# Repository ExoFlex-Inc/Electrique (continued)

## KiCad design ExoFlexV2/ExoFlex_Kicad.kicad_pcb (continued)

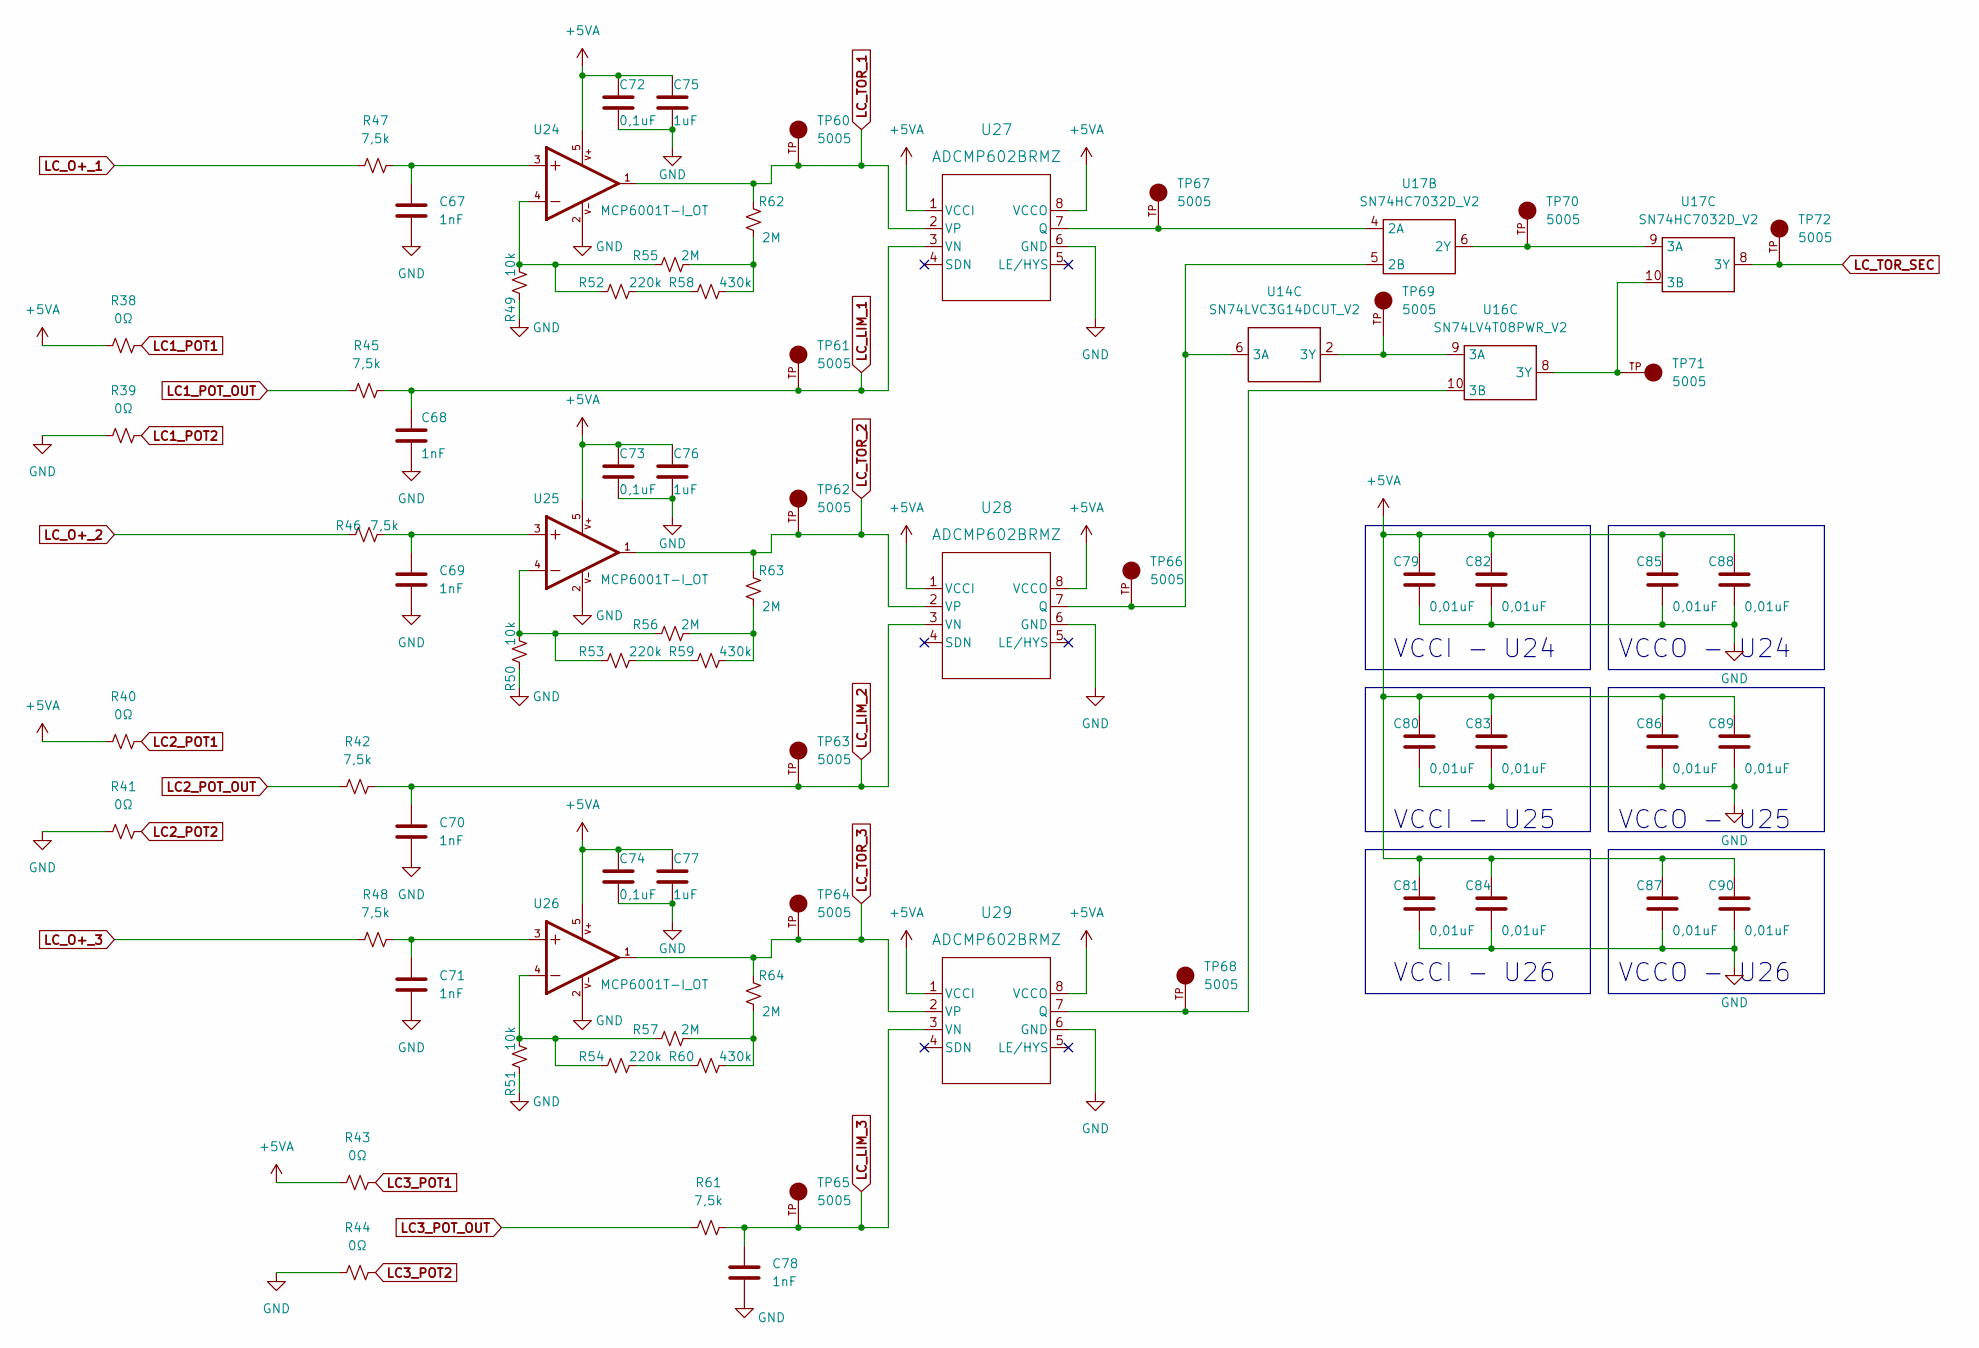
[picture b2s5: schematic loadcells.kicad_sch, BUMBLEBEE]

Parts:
C67, C68, C69, C70, C71, C78: 1nF; C_0603_1608Metric
C72, C73, C74: 0,1uF; C_0603_1608Metric
C75, C76, C77: 1uF; C_0603_1608Metric
C79, C80, C81, C82, C83, C84, C85, C86, C87, C88, C89, C90: 0,01uF; C_0603_1608Metric
R38, R39, R40, R41, R43, R44: 0Ω; R_0603_1608Metric
R42, R45, R46, R47, R48, R61: 7,5k; R_0603_1608Metric
R49, R50, R51: 10k; R_0603_1608Metric
R52, R53, R54: 220k; R_0603_1608Metric
R55, R56, R57, R62, R63, R64: 2M; R_0603_1608Metric
R58, R59, R60: 430k; R_0603_1608Metric
TP60, TP61, TP62, TP63, TP64, TP65, TP66, TP67, TP68, TP69, TP70, TP71, TP72: 5005; KEYSTONE_5005
U14: SN74LVC3G14DCUT_V2; SN74LVC3G14DCUT
U16: SN74LV4T08PWR_V2; SN74LV4T08PWR
U17: SN74HC7032D_V2; SN74HC7032D
U24, U25, U26: MCP6001T-I_OT; SOT95P270X145-5N
U27, U28, U29: ADCMP602BRMZ

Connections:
+5VA: C72.1, C73.1, C74.1, C75.1, C76.1, C77.1, C79.1, C80.1, C81.1, C82.1, C83.1, C84.1, C85.1, C86.1, C87.1, C88.1, C89.1, C90.1, R38.1, R40.1, R43.1, U24.5, U25.5, U26.5, U27.1 (VCCI), U27.8 (VCCO), U28.1 (VCCI), U28.8 (VCCO), U29.1 (VCCI), U29.8 (VCCO); also elsewhere on the board
LC1_POT1: R38.2; also elsewhere on the board
LC1_POT2: R39.2; also elsewhere on the board
LC1_POT_OUT: R45.1; also elsewhere on the board
LC2_POT1: R40.2; also elsewhere on the board
LC2_POT2: R41.2; also elsewhere on the board
LC2_POT_OUT: R42.1; also elsewhere on the board
LC3_POT1: R43.2; also elsewhere on the board
LC3_POT2: R44.2; also elsewhere on the board
LC3_POT_OUT: R61.1; also elsewhere on the board
LC_LIM_1: C68.1, R45.2, TP61.TP, U27.3 (VN); also elsewhere on the board
LC_LIM_2: C70.1, R42.2, TP63.TP, U28.3 (VN); also elsewhere on the board
LC_LIM_3: C78.1, R61.2, TP65.TP, U29.3 (VN); also elsewhere on the board
LC_O+_1: R47.1; also elsewhere on the board
LC_O+_2: R46.1; also elsewhere on the board
LC_O+_3: R48.1; also elsewhere on the board
LC_TOR_1: R62.2, TP60.TP, U24.1, U27.2 (VP); also elsewhere on the board
LC_TOR_2: R63.2, TP62.TP, U25.1, U28.2 (VP); also elsewhere on the board
LC_TOR_3: R64.2, TP64.TP, U26.1, U29.2 (VP); also elsewhere on the board
LC_TOR_SEC: TP72.TP, U17.8 (3Y); also elsewhere on the board
unnamed: C67.1, R47.2, U24.3
unnamed: C69.1, R46.2, U25.3
unnamed: C71.1, R48.2, U26.3
unnamed: R49.2, R52.1, R55.1, U24.4
unnamed: R50.2, R53.1, R56.1, U25.4
unnamed: R51.2, R54.1, R57.1, U26.4
unnamed: R52.2, R58.1
unnamed: R53.2, R59.1
unnamed: R54.2, R60.1
unnamed: R55.2, R58.2, R62.1
unnamed: R56.2, R59.2, R63.1
unnamed: R57.2, R60.2, R64.1
unnamed: TP66.TP, U14.6 (3A), U17.5 (2B), U28.7 (Q)
unnamed: TP67.TP, U17.4 (2A), U27.7 (Q)
unnamed: TP68.TP, U16.10 (3B), U29.7 (Q)
unnamed: TP69.TP, U14.2 (3Y), U16.9 (3A)
unnamed: TP70.TP, U17.6 (2Y), U17.9 (3A)
unnamed: TP71.TP, U16.8 (3Y), U17.10 (3B)

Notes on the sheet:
VCCO - U26
VCCI - U26
VCCO - U25
VCCI - U25
VCCI - U24
VCCO - U24

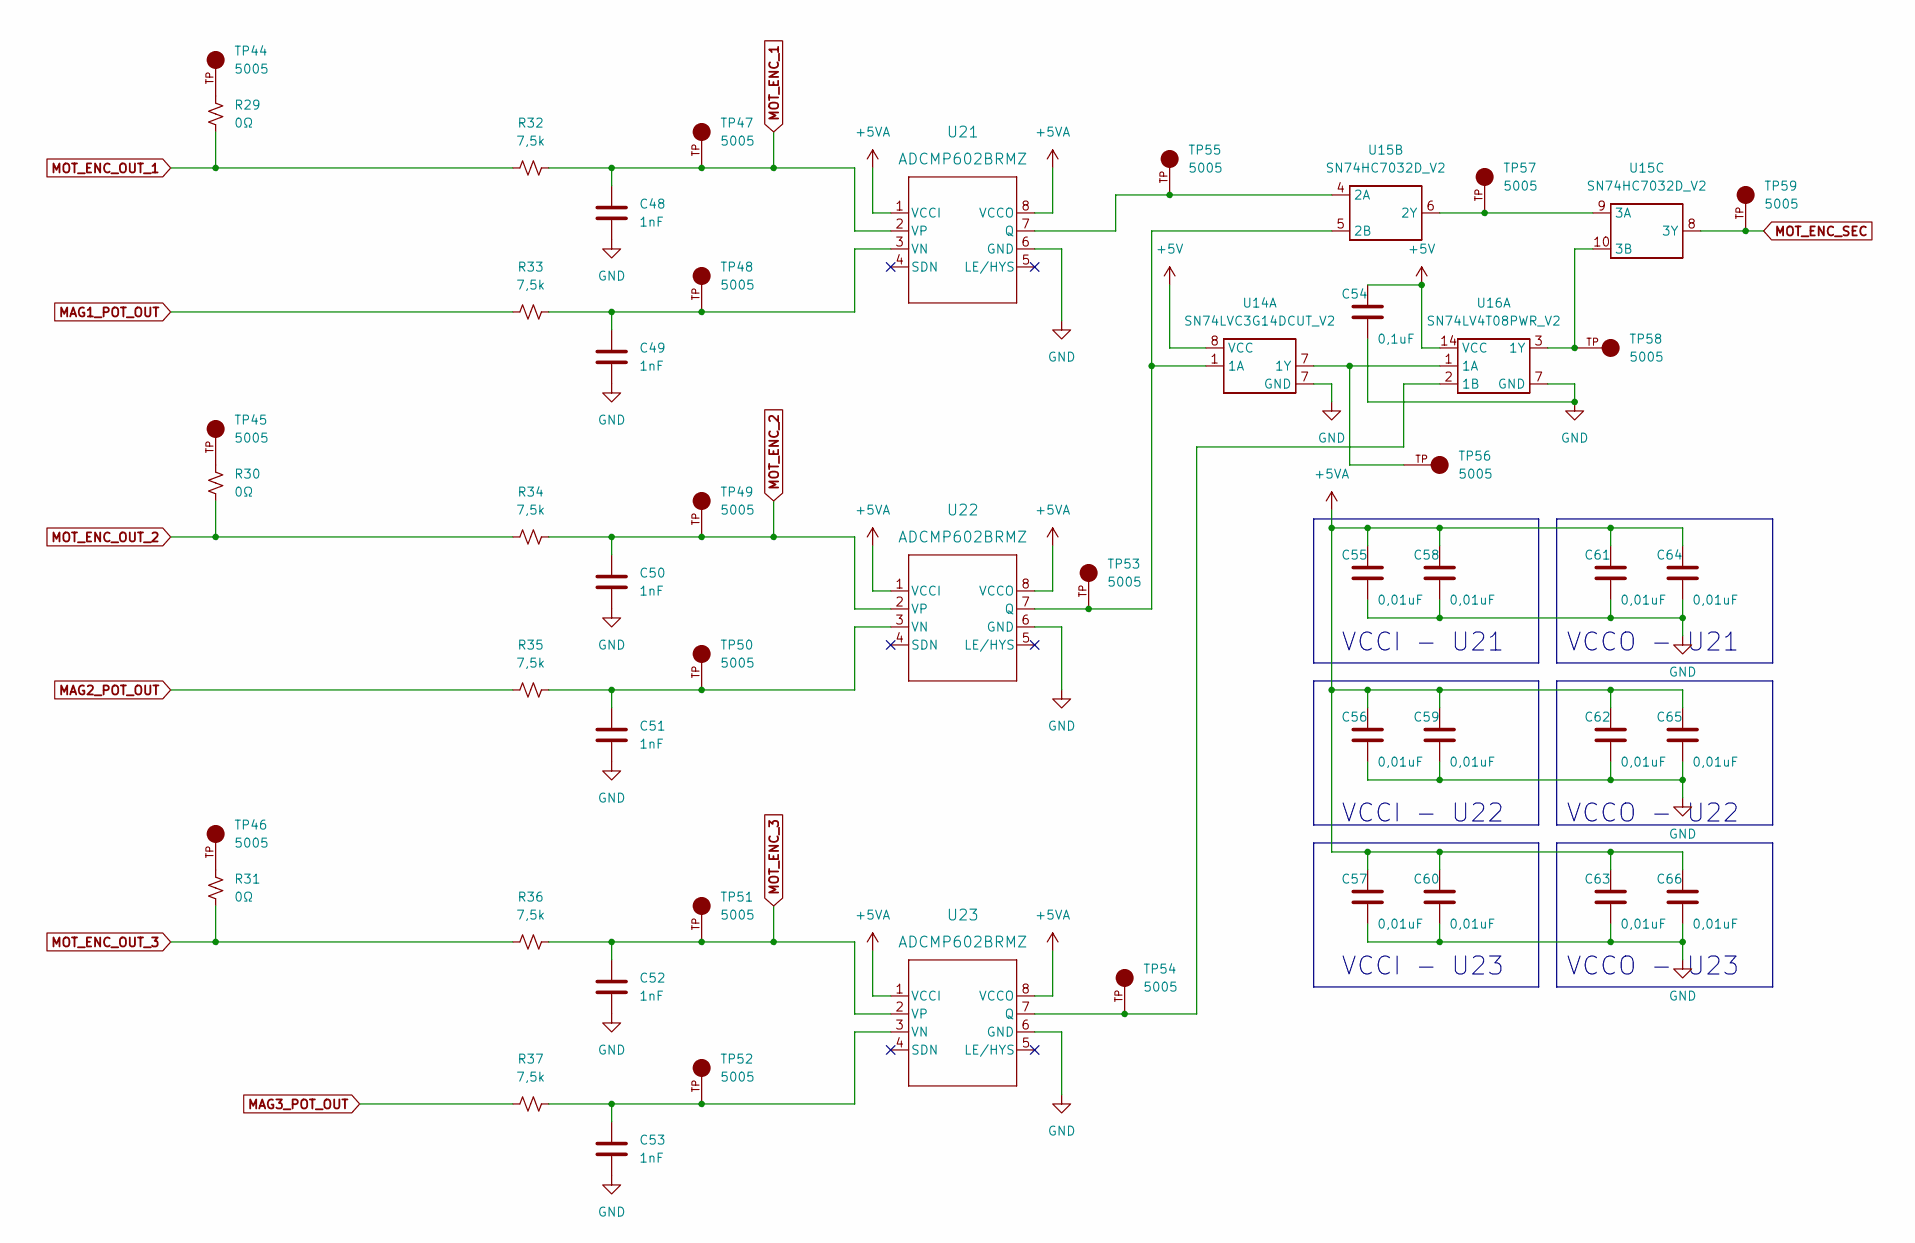
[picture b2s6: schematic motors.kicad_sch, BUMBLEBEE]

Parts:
C48, C49, C50, C51, C52, C53: 1nF; C_0603_1608Metric
C54: 0,1uF; C_0603_1608Metric
C55, C56, C57, C58, C59, C60, C61, C62, C63, C64, C65, C66: 0,01uF; C_0603_1608Metric
R29, R30, R31: 0Ω; R_0603_1608Metric
R32, R33, R34, R35, R36, R37: 7,5k; R_0603_1608Metric
TP44, TP45, TP46, TP47, TP48, TP49, TP50, TP51, TP52, TP53, TP54, TP55, TP56, TP57, TP58, TP59: 5005; KEYSTONE_5005
U14: SN74LVC3G14DCUT_V2; SN74LVC3G14DCUT
U15: SN74HC7032D_V2; SN74HC7032D
U16: SN74LV4T08PWR_V2; SN74LV4T08PWR
U21, U22, U23: ADCMP602BRMZ

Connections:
+5VA: C55.1, C56.1, C57.1, C58.1, C59.1, C60.1, C61.1, C62.1, C63.1, C64.1, C65.1, C66.1, U21.1 (VCCI), U21.8 (VCCO), U22.1 (VCCI), U22.8 (VCCO), U23.1 (VCCI), U23.8 (VCCO); also elsewhere on the board
MAG1_POT_OUT: R33.1; also elsewhere on the board
MAG2_POT_OUT: R35.1; also elsewhere on the board
MAG3_POT_OUT: R37.1; also elsewhere on the board
MOT_ENC_1: C48.1, R32.2, TP47.TP, U21.2 (VP)
MOT_ENC_2: C50.1, R34.2, TP49.TP, U22.2 (VP)
MOT_ENC_3: C52.1, R36.2, TP51.TP, U23.2 (VP)
MOT_ENC_OUT_1: R29.2, R32.1; also elsewhere on the board
MOT_ENC_OUT_2: R30.2, R34.1; also elsewhere on the board
MOT_ENC_OUT_3: R31.2, R36.1; also elsewhere on the board
MOT_ENC_SEC: TP59.TP, U15.8 (3Y); also elsewhere on the board
unnamed: C49.1, R33.2, TP48.TP, U21.3 (VN)
unnamed: C51.1, R35.2, TP50.TP, U22.3 (VN)
unnamed: C53.1, R37.2, TP52.TP, U23.3 (VN)
unnamed: R29.1, TP44.TP
unnamed: R30.1, TP45.TP
unnamed: R31.1, TP46.TP
unnamed: TP53.TP, U14.1 (1A), U15.5 (2B), U22.7 (Q)
unnamed: TP54.TP, U16.2 (1B), U23.7 (Q)
unnamed: TP55.TP, U15.4 (2A), U21.7 (Q)
unnamed: TP57.TP, U15.6 (2Y), U15.9 (3A)
unnamed: TP58.TP, U15.10 (3B), U16.3 (1Y)

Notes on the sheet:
VCCI - U21
VCCO - U21
VCCI - U22
VCCO - U22
VCCI - U23
VCCO - U23

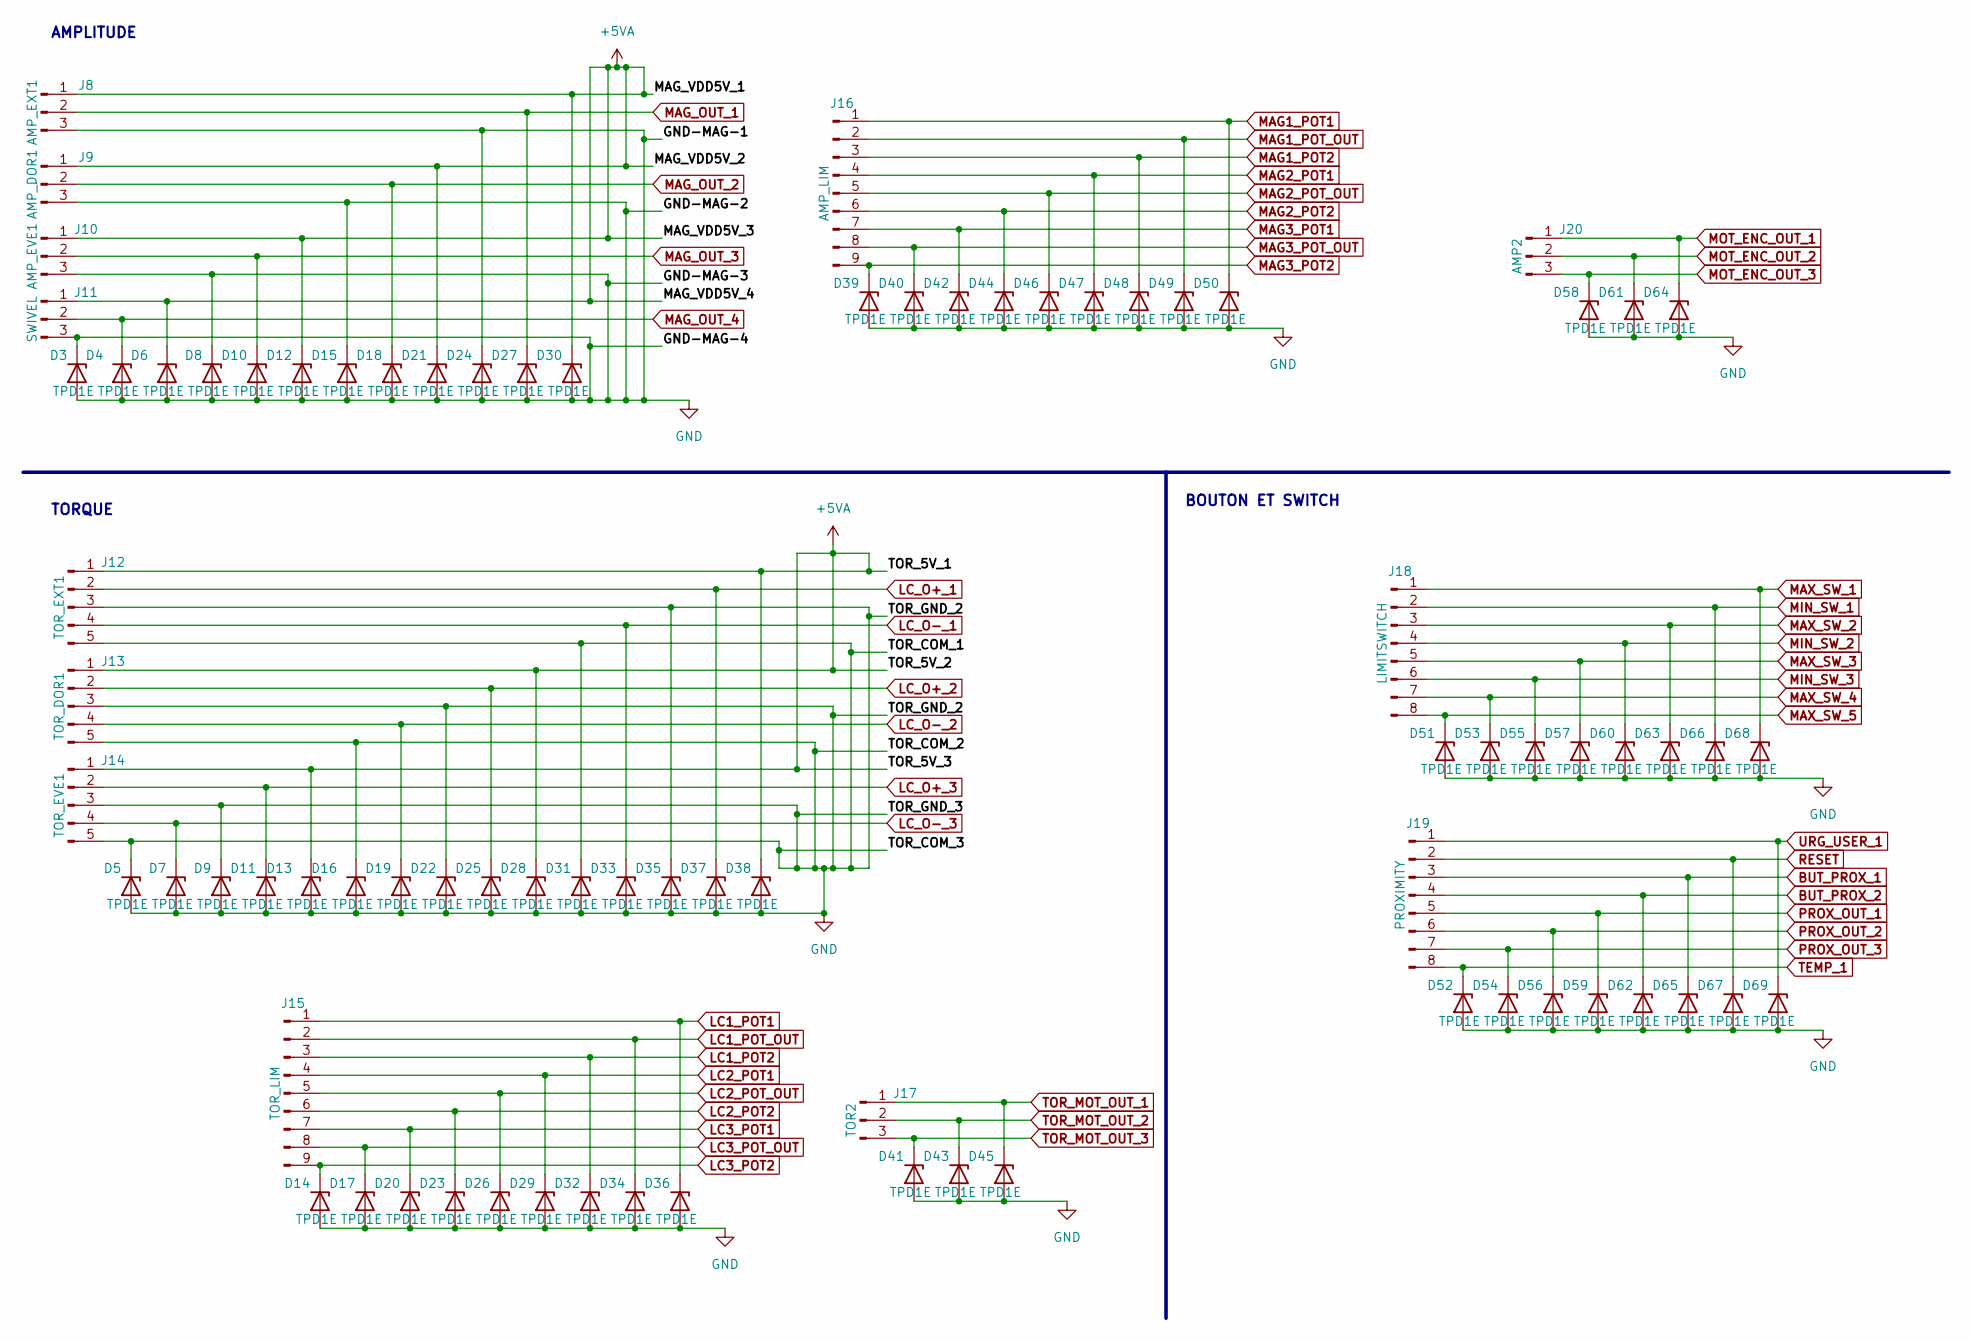
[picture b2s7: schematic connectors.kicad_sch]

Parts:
D3, D4, D5, D6, D7, D8, D9, D10, D11, D12, D13, D14, D15, D16, D17, D18, D19, D20, D21, D22, D23, D24, D25, D26, D27, D28, D29, D30, D31, D32, D33, D34, D35, D36, D37, D38, D39, D40, D41, D42, D43, D44, D45, D46, D47, D48, D49, D50, D51, D52, D53, D54, D55, D56, D57, D58, D59, D60, D61, D62, D63, D64, D65, D66, D67, D68, D69: TPD1E; DPY2_TEX
J8: AMP_EXT1; PinHeader_1x03_P2.54mm_Vertical
J9: AMP_DOR1; PinHeader_1x03_P2.54mm_Vertical
J10: AMP_EVE1; PinHeader_1x03_P2.54mm_Vertical
J11: SWIVEL; PinHeader_1x03_P2.54mm_Vertical
J12: TOR_EXT1; PinHeader_1x05_P2.54mm_Vertical
J13: TOR_DOR1; PinHeader_1x05_P2.54mm_Vertical
J14: TOR_EVE1; PinHeader_1x05_P2.54mm_Vertical
J15: TOR_LIM; PinHeader_1x09_P2.54mm_Vertical
J16: AMP_LIM; PinHeader_1x09_P2.54mm_Vertical
J17: TOR2; PinHeader_1x03_P2.54mm_Vertical
J18: LIMITSWITCH; PinHeader_1x08_P2.54mm_Vertical
J19: PROXIMITY; PinHeader_1x08_P2.54mm_Vertical
J20: AMP2; PinHeader_1x03_P2.54mm_Vertical

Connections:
+5VA: D6.1 (K), D12.1 (K), D13.1 (K), D21.1 (K), D28.1 (K), D30.1 (K), D38.1 (K), J8.1, J9.1, J10.1, J11.1, J12.1, J13.1, J14.1; also elsewhere on the board
BUT_PROX_1: D65.1 (K), J19.3; also elsewhere on the board
BUT_PROX_2: D62.1 (K), J19.4; also elsewhere on the board
LC1_POT1: D36.1 (K), J15.1; also elsewhere on the board
LC1_POT2: D32.1 (K), J15.3; also elsewhere on the board
LC1_POT_OUT: D34.1 (K), J15.2; also elsewhere on the board
LC2_POT1: D29.1 (K), J15.4; also elsewhere on the board
LC2_POT2: D23.1 (K), J15.6; also elsewhere on the board
LC2_POT_OUT: D26.1 (K), J15.5; also elsewhere on the board
LC3_POT1: D20.1 (K), J15.7; also elsewhere on the board
LC3_POT2: D14.1 (K), J15.9; also elsewhere on the board
LC3_POT_OUT: D17.1 (K), J15.8; also elsewhere on the board
LC_O+_1: D37.1 (K), J12.2; also elsewhere on the board
LC_O+_2: D25.1 (K), J13.2; also elsewhere on the board
LC_O+_3: D11.1 (K), J14.2; also elsewhere on the board
LC_O-_1: D33.1 (K), J12.4
LC_O-_2: D19.1 (K), J13.4
LC_O-_3: D7.1 (K), J14.4
MAG1_POT1: D50.1 (K), J16.1; also elsewhere on the board
MAG1_POT2: D48.1 (K), J16.3; also elsewhere on the board
MAG1_POT_OUT: D49.1 (K), J16.2; also elsewhere on the board
MAG2_POT1: D47.1 (K), J16.4; also elsewhere on the board
MAG2_POT2: D44.1 (K), J16.6; also elsewhere on the board
MAG2_POT_OUT: D46.1 (K), J16.5; also elsewhere on the board
MAG3_POT1: D42.1 (K), J16.7; also elsewhere on the board
MAG3_POT2: D39.1 (K), J16.9; also elsewhere on the board
MAG3_POT_OUT: D40.1 (K), J16.8; also elsewhere on the board
MAG_OUT_1: D27.1 (K), J8.2; also elsewhere on the board
MAG_OUT_2: D18.1 (K), J9.2; also elsewhere on the board
MAG_OUT_3: D10.1 (K), J10.2; also elsewhere on the board
MAG_OUT_4: D4.1 (K), J11.2; also elsewhere on the board
MAX_SW_1: D68.1 (K), J18.1; also elsewhere on the board
MAX_SW_2: D63.1 (K), J18.3; also elsewhere on the board
MAX_SW_3: D57.1 (K), J18.5; also elsewhere on the board
MAX_SW_4: D53.1 (K), J18.7; also elsewhere on the board
MAX_SW_5: D51.1 (K), J18.8; also elsewhere on the board
MIN_SW_1: D66.1 (K), J18.2; also elsewhere on the board
MIN_SW_2: D60.1 (K), J18.4; also elsewhere on the board
MIN_SW_3: D55.1 (K), J18.6; also elsewhere on the board
MOT_ENC_OUT_1: D64.1 (K), J20.1; also elsewhere on the board
MOT_ENC_OUT_2: D61.1 (K), J20.2; also elsewhere on the board
MOT_ENC_OUT_3: D58.1 (K), J20.3; also elsewhere on the board
PROX_OUT_1: D59.1 (K), J19.5; also elsewhere on the board
PROX_OUT_2: D56.1 (K), J19.6; also elsewhere on the board
PROX_OUT_3: D54.1 (K), J19.7; also elsewhere on the board
RESET: D67.1 (K), J19.2; also elsewhere on the board
TEMP_1: D52.1 (K), J19.8; also elsewhere on the board
TOR_MOT_OUT_1: D45.1 (K), J17.1; also elsewhere on the board
TOR_MOT_OUT_2: D43.1 (K), J17.2; also elsewhere on the board
TOR_MOT_OUT_3: D41.1 (K), J17.3; also elsewhere on the board
URG_USER_1: D69.1 (K), J19.1; also elsewhere on the board

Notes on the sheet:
BOUTON ET SWITCH
TORQUE
AMPLITUDE

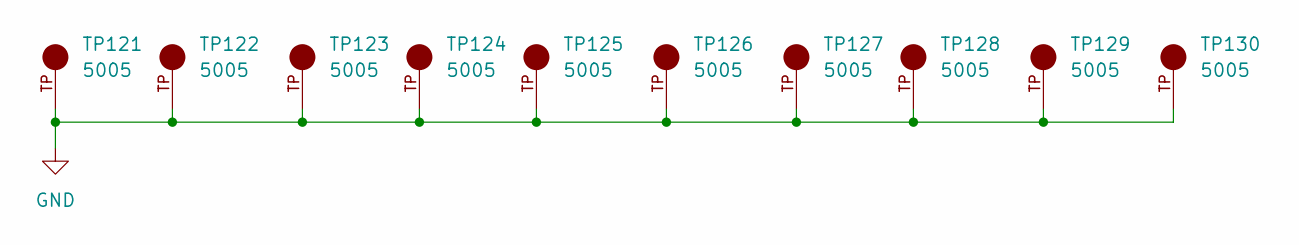
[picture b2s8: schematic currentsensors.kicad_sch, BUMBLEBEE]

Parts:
TP121, TP122, TP123, TP124, TP125, TP126, TP127, TP128, TP129, TP130: 5005; KEYSTONE_5005

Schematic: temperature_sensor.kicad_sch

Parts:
C128, C129: 1nF; C_0603_1608Metric
C130, C131, C132, C133: 0,01uF; C_0603_1608Metric
R91, R93, R94: 0Ω; R_0603_1608Metric
R92, R95: 7,5k; R_0603_1608Metric
TP118, TP119, TP120: 5005; KEYSTONE_5005
U38: ADCMP602BRMZ

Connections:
+5VA: C130.1, C131.1, C132.1, C133.1, R93.1, U38.1 (VCCI), U38.8 (VCCO); also elsewhere on the board
unnamed: C129.1, R95.2, U38.3 (VN)
unnamed: R91.1, TP118.TP
unnamed: R93.2, R94.2, R95.1
TEMP_1: C128.1, R92.2, TP119.TP, U38.2 (VP); also elsewhere on the board
TEMP_OUT_1: R91.2, R92.1
TEMP_SEC: TP120.TP, U38.7 (Q); also elsewhere on the board

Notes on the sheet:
VCCO - U41
VCCI - U41

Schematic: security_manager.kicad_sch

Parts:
C18, C19, C20: 1uF; C_0603_1608Metric
TP10, TP11, TP12, TP13, TP14, TP15, TP16, TP17, TP18, TP19: 5005; KEYSTONE_5005
U7, U8: SN74HC7032D_V2; SN74HC7032D
U9, U10: SN74LV4T08PWR_V2; SN74LV4T08PWR

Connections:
ALIM_SEC: U7.3 (1Y); also elsewhere on the board
BUT_PROX_SEC: U8.13 (4B); also elsewhere on the board
LC_TOR_SEC: U8.1 (1A); also elsewhere on the board
LEFTRIGHT_SEC: U10.2 (1B); also elsewhere on the board
MAG_AMP_SEC: U7.5 (2B); also elsewhere on the board
MOT_ENC_SEC: U7.4 (2A); also elsewhere on the board
unnamed: TP10.TP, U7.6 (2Y), U7.9 (3A)
unnamed: TP11.TP, U7.2 (1B), U7.11 (4Y)
unnamed: TP12.TP, U7.8 (3Y), U9.9 (3A)
unnamed: TP13.TP, U8.3 (1Y), U9.13 (4B)
unnamed: TP14.TP, U8.11 (4Y), U9.10 (3B), U9.12 (4A), U10.1 (1A)
unnamed: TP15.TP, U8.4 (2A), U9.8 (3Y)
unnamed: TP16.TP, U8.5 (2B), U9.11 (4Y)
unnamed: TP17.TP, U8.6 (2Y), U8.9 (3A)
unnamed: TP18.TP, U8.10 (3B), U10.3 (1Y)
unnamed: TP19.TP, U7.1 (1A), U8.8 (3Y)
PROX_SEC: U8.12 (4A); also elsewhere on the board
SW-SEC: U7.10 (3B); also elsewhere on the board
TEMP_SEC: U7.13 (4B); also elsewhere on the board
TOR_MOT_SEC: U8.2 (1B); also elsewhere on the board
URG_SEC: U7.12 (4A); also elsewhere on the board

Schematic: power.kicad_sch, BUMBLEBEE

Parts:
C1, C10, C13, C14, C15, C16, C17: 10uF; C_0603_1608Metric
C2: 150uF 50V; CAP_EEHZS1H151P
C3: 10 uF; C_0805_2012Metric
C4, C7: 0,047uF; C_0603_1608Metric
C5: 100uF 20V; CAP_PC_8X7_NCH
C6: 220uF 50V; CAP_EEHZS1H221P
C8: 100uF; C_1210_3225Metric
C9: 220uF 20V; CAP_20SVPK220M
C11: 1uF; C_0603_1608Metric
C12: 47uF; C_1206_3216Metric
CR1: 1SS321_LF
CR2: TBAT54_LM
D1: TPD1E; DPY2_TEX
D2: SS12P2L-M3_86A; DIO_SS12P2L-M3_86A
F1: FSF5X20 200mA; 696108003002
F2: FSF5X20 500mA; 696108003002
J1, J3: 24V; TerminalBlock14AWG
J2: 5V; TerminalBlock14AWG
K1: UD2-5NU; UD2_NU_KEM-L
R1: 5k; R_0603_1608Metric
R2: 1,5k; R_0603_1608Metric
R3: 1,1k; R_0603_1608Metric
R4: 6,8k; R_0603_1608Metric
R5: RE1C002UNTCL; DIO_RB558WMF_ROM
R6: 23,7; R_0603_1608Metric
R7: 25,5k 1%; R_0603_1608Metric
R8: 10k; R_0603_1608Metric
TP1, TP2, TP3, TP4, TP5, TP6, TP7, TP8, TP9, TP131: 5005; KEYSTONE_5005
U1: PTSM36ADBZR; SOT-23-3_DBZ_TEX
U2: STPS20M100SG-TR; D2PAK_STM
U3: 74LV244PW; DB20
U4: CD4044BPWR
U5: LMZ23603TZ_NOPB; LMZ23603
U6: TPS7A4701RGWR; TPS7A470; PARTREV 4204100/C 07/11

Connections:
+5VA: C12.1, C13.1, C14.1, C15.1, C16.1, C17.1, R8.1, TP9.TP, U6.1 (OUT_1); also elsewhere on the board
+24V: C2.1, C3.1, C4.1, C6.1, F1.2, K1.2, TP3.TP, U1.3 (IO), U2.3, U5.1 (VIN)
/POWER/5V_IN: F2.1, J2.2
/POWER/24V_IN: F1.1, J1.2
/POWER/24V_OUT: CR2.3 (C), J3.1, K1.4, TP6.TP
/POWER/COIL-: CR1.1 (A), CR1.2 (A), K1.1, R5.3 (D), TP8.TP
/POWER/LATCH_Q1: R5.1 (G), TP5.TP, U4.13 (Q1)
ALIM_SEC: TP4.TP, U4.3 (S1); also elsewhere on the board
unnamed: C1.1, R1.2, U3.4 (1A1)
unnamed: C7.1, C8.1, C9.1, C10.1, R6.2, TP7.TP, U5.7 (VOUT), U6.13 (EN), U6.15 (IN_15)
unnamed: C11.1, U6.14 (NR)
unnamed: R2.2, U5.2 (SYNC)
unnamed: R3.2, R4.1, U5.5 (FB)
unnamed: R4.2, R6.1
unnamed: R7.2, R8.2, U6.3 (SENSE/FB)
unnamed: TP2.TP, TP131.TP, U3.16 (1Y1), U4.4 (R1)
RESET: R1.1; also elsewhere on the board

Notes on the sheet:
Vers le contacteur

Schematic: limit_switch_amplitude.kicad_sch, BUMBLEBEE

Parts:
C40, C41, C42, C43, C44, C45, C46: 10uF; C_0603_1608Metric
C47: 0,1uF; C_0603_1608Metric
R22, R23, R24, R25, R26, R27, R28: 5k; R_0603_1608Metric
TP33, TP34, TP35, TP36, TP37, TP38, TP39, TP40, TP41, TP42, TP43: 5005; KEYSTONE_5005
U3, U18: 74LV244PW; DB20
U16: SN74LV4T08PWR_V2; SN74LV4T08PWR
U17, U20: SN74HC7032D_V2; SN74HC7032D
U19: SN74LVC3G14DCUT_V2; SN74LVC3G14DCUT

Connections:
MAX_SW_1: R22.1; also elsewhere on the board
MAX_SW_2: R23.1; also elsewhere on the board
MAX_SW_3: R24.1; also elsewhere on the board
MIN_SW_1: R25.1; also elsewhere on the board
MIN_SW_2: R26.1; also elsewhere on the board
MIN_SW_3: R27.1; also elsewhere on the board
unnamed: C40.1, R22.2, U18.2 (1A0)
unnamed: C41.1, R23.2, U18.6 (1A2)
unnamed: C42.1, R24.2, U18.17 (2A0)
unnamed: C43.1, R25.2, U18.4 (1A1)
unnamed: C44.1, R26.2, U18.8 (1A3)
unnamed: C45.1, R27.2, U18.15 (2A1)
unnamed: C46.1, R28.2, U3.2 (1A0)
unnamed: TP41.TP, U17.11 (4Y), U20.1 (1A)
unnamed: TP42.TP, U16.11 (4Y), U20.2 (1B)
SW-SEC: TP43.TP, U20.3 (1Y); also elsewhere on the board
SWMAX1: TP33.TP, U17.12 (4A), U18.18 (1Y0); also elsewhere on the board
SWMAX2: TP34.TP, U17.13 (4B), U18.14 (1Y2), U19.1 (1A); also elsewhere on the board
SWMAX3: TP35.TP, U16.13 (4B), U18.3 (2Y0); also elsewhere on the board
SWMIN1: TP36.TP, U18.16 (1Y1); also elsewhere on the board
SWMIN2: TP37.TP, U18.12 (1Y3); also elsewhere on the board
SWMIN3: TP38.TP, U18.5 (2Y1); also elsewhere on the board
URG_SEC: TP39.TP, U3.18 (1Y0); also elsewhere on the board
URG_USER_1: R28.1; also elsewhere on the board

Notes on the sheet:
Tension : 250V Courant : 5A Terminal : SPDT

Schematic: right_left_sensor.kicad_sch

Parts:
C110: 1nF; C_0603_1608Metric
C111, C112: 10uF; C_0603_1608Metric
C113: 0,1uF; C_0603_1608Metric
C114, C115, C116, C117, C118, C119, C120, C121: 0,01uF; C_0603_1608Metric
R74, R75: 5k; R_0603_1608Metric
R76: 7,5k; R_0603_1608Metric
R77, R78, R79, R80: 0Ω; R_0603_1608Metric
TP89, TP90, TP91, TP92, TP93, TP94, TP95, TP96, TP97, TP98, TP99, TP100, TP101, TP102: 5005; KEYSTONE_5005
U10, U34: SN74LV4T08PWR_V2; SN74LV4T08PWR
U18: 74LV244PW; DB20
U19: SN74LVC3G14DCUT_V2; SN74LVC3G14DCUT
U20: SN74HC7032D_V2; SN74HC7032D
U36, U37: ADCMP602BRMZ

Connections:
+5VA: C114.1, C115.1, C116.1, C117.1, C118.1, C119.1, C120.1, C121.1, R77.2, R79.2, U36.1 (VCCI), U36.8 (VCCO), U37.1 (VCCI), U37.8 (VCCO); also elsewhere on the board
LEFTRIGHT_SEC: TP102.TP, U20.8 (3Y); also elsewhere on the board
MAG_AMP_4: C110.1, R76.2, TP93.TP, U36.2 (VP), U37.3 (VN); also elsewhere on the board
MAG_OUT_4: R76.1; also elsewhere on the board
MAX_SW_4: R74.1; also elsewhere on the board
MAX_SW_5: R75.1; also elsewhere on the board
unnamed: C111.1, R74.2, U18.13 (2A2)
unnamed: C112.1, R75.2, U18.11 (2A3)
unnamed: R77.1, R78.2, TP89.TP, U36.3 (VN)
unnamed: R79.1, R80.2, TP90.TP, U37.2 (VP)
unnamed: TP94.TP, U19.5 (2Y), U34.1 (1A)
unnamed: TP95.TP, U10.9 (3A), U36.7 (Q)
unnamed: TP96.TP, U10.10 (3B), U37.7 (Q)
unnamed: TP97.TP, U19.2 (3Y), U34.2 (1B)
unnamed: TP98.TP, U20.4 (2A), U34.3 (1Y)
unnamed: TP99.TP, U20.5 (2B), U34.6 (2Y)
unnamed: TP100.TP, U10.8 (3Y), U20.10 (3B)
unnamed: TP101.TP, U20.6 (2Y), U20.9 (3A)
SWMAX4: TP91.TP, U18.7 (2Y2), U19.3 (2A), U34.4 (2A); also elsewhere on the board
SWMAX5: TP92.TP, U18.9 (2Y3), U19.6 (3A), U34.5 (2B); also elsewhere on the board

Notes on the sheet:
VCCI - U35
VCCO - U35

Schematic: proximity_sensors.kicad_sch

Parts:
C122, C123, C124, C125, C126: 10uF; C_0603_1608Metric
C127: 0,1uF; C_0603_1608Metric
R81, R82, R83, R84, R85: 0Ω; R_0603_1608Metric
R86, R87, R88, R89, R90: 5k; R_0603_1608Metric
TP103, TP104, TP105, TP106, TP107, TP108, TP109, TP110, TP111, TP112, TP113, TP114, TP115, TP116, TP117: 5005; KEYSTONE_5005
U3: 74LV244PW; DB20
U9, U34: SN74LV4T08PWR_V2; SN74LV4T08PWR
U33: SN74LVC3G14DCUT_V2; SN74LVC3G14DCUT
U35: SN74HC7032D_V2; SN74HC7032D

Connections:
BUT_PROX_1: R84.2, R89.1; also elsewhere on the board
BUT_PROX_2: R85.2, R90.1; also elsewhere on the board
BUT_PROX_SEC: TP117.TP, U9.3 (1Y); also elsewhere on the board
unnamed: C122.1, R86.2, U3.17 (2A0)
unnamed: C123.1, R87.2, U3.15 (2A1)
unnamed: C124.1, R88.2, U3.13 (2A2)
unnamed: C125.1, R89.2, U3.6 (1A2)
unnamed: C126.1, R90.2, U3.8 (1A3)
unnamed: R81.1, TP103.TP
unnamed: R82.1, TP104.TP
unnamed: R83.1, TP105.TP
unnamed: R84.1, TP106.TP
unnamed: R85.1, TP107.TP
unnamed: TP113.TP, U33.5 (2Y), U34.12 (4A)
unnamed: TP114.TP, U35.6 (2Y), U35.9 (3A)
unnamed: TP115.TP, U34.11 (4Y), U35.10 (3B)
PROX_1: TP108.TP, U3.3 (2Y0), U35.4 (2A); also elsewhere on the board
PROX_2: TP109.TP, U3.5 (2Y1), U33.3 (2A), U35.5 (2B); also elsewhere on the board
PROX_3: TP110.TP, U3.7 (2Y2), U34.13 (4B); also elsewhere on the board
PROX_4: TP111.TP, U3.14 (1Y2), U9.1 (1A); also elsewhere on the board
PROX_5: TP112.TP, U3.12 (1Y3), U9.2 (1B); also elsewhere on the board
PROX_OUT_1: R81.2, R86.1; also elsewhere on the board
PROX_OUT_2: R82.2, R87.1; also elsewhere on the board
PROX_OUT_3: R83.2, R88.1; also elsewhere on the board
PROX_SEC: TP116.TP, U35.8 (3Y); also elsewhere on the board

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
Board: 2 copper layers, 491 parts (77 on the bottom side), 208 nets, no tracks yet.

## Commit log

2023-07-25 push elec folders
2023-07-27 push code elec
2023-10-16 Ajout des capteurs de courant, loadcell et potentiomètre et remplacement du stm32 par Raspberry Pi 4
2023-10-21 Backup du stm32
2024-02-05 Plein de modification
    Beaucoup trop pour que le commit soit intéressant
2024-02-07 Schematic structure
    Ajout des Encodeur magnétique et load cells, début de circuit de comparateurs
2024-02-15 Sensor modification
    Add load cell and magnetic encoder structure for the logic
2024-03-21 Many changes
    Debouncing, power protection, potentiometer limits, etc.
2024-03-28 quque truc
2024-03-31 Placement
    Début du placement et modification d'après dernier review
2024-04-01 Placement encore
2024-04-01 Placement done V1
2024-06-27 Mise à jour mi-stage
    - Torque et Amplitude testé et vérifié
    - Capteur de présence et de proximité testé
    - Système de détection de coupure de fils
    - Polyvalence pour plusieurs capteurs
2024-06-27 Mise à jour signaux STM
    - Condo de découplage
    - Signaux supplémentaire pour le STM
    - Page GND sera pour Multiplexeur
2024-06-28 Gestion de multiple signaux
    - Ajout de multiplexeur 8:1 pour les signaux analogique supplémentaire
    - Ajout de multiplexeur 8:1 arranger sous forme d'un 32:1
    - Ajout du footprint pour le mux choisis
2024-07-10 Finalisation 1
    - Ajout de pages pour la gestion des signaux négatif
    - Modification des pages de torque et amplitude
2024-07-10 Finalisation 2
    -Ajout des nouveaux comparateurs
    - Ajout d'une page découplage
    - Retrait des condensateur dans les autres pages
    - Ajout de trimmer pour les résistance importante mais incertaines
2024-07-11 Chokes et RC
    - Ajout des RF chokes
    - Changement des résistance pour 0805
2024-07-11 Trimmer et jumper
    -Changement de symbole de jumper
    -Ajout des des trimmer aux endroits nécessaires
2024-07-12 Test points et notes
    - Ajout de tous les tests point nécessaires
    - Ajoute des sections de notes dans chaque page
2024-07-17 Schématisation terminée
    - Schéma terminé
    - Passage vers le PCB
2024-07-18 Bug NetList
    - Ajout de net-tie pour les GND et et les +5V
2024-07-18 PLACEMENT 1
    - Placement des connnecteurs
2024-07-29 Finalisation 3
    - Changement des régulateur de tension
    - Retrait de test point inutile
    - Changement de jumper mal positionner
    - Ajout de Mounting holes et fiducial
2024-08-03 Finalisation schéma FIN
    - Changement des uméro pour les inverseurs
    - Changement des connecteur et début de placement
2024-08-05 Placement 1
    - Placement de tous les connecteur
    - Placement de tous les test point
2024-08-06 PLacement 2
    - Puissance
    - signaux
    -
2024-08-08 Modification Schéma + Layout
    - Ajout de RC potentiel entre les capteur de torque et l'ampli d'instru
2024-08-08 Vias
    - Vias de ground et puissance terminés
2024-08-09 Routage 3
    - Routage des connecteurs terminé
    - Routage des signaux terminé
2024-08-09 Routage Fin
    - Alimentation router
    - Urg Sec dans le OR gate vers Alim Sec
    - Changement d'un condo
2024-08-12 Routage pour Review 1
    - Replacement des test point pour faciliter le rework
    - Correction des erreurs dans le BOM
    -
2024-08-14 Layout Review 1
    - Routing fone Alimentation et ADC
2024-08-14 Routing final 3
    - Some stuff
2024-08-29 Final
2024-09-12 LAst changes
2025-02-27 Analyse Post-PMC
    -Modification du footprint du régulateur de tension
    - Inversion des condos et diode sur les tensions négative
